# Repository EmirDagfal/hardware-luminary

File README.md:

# hardware-luminary
Diseño PCB en kicad de fotocelula LoRa

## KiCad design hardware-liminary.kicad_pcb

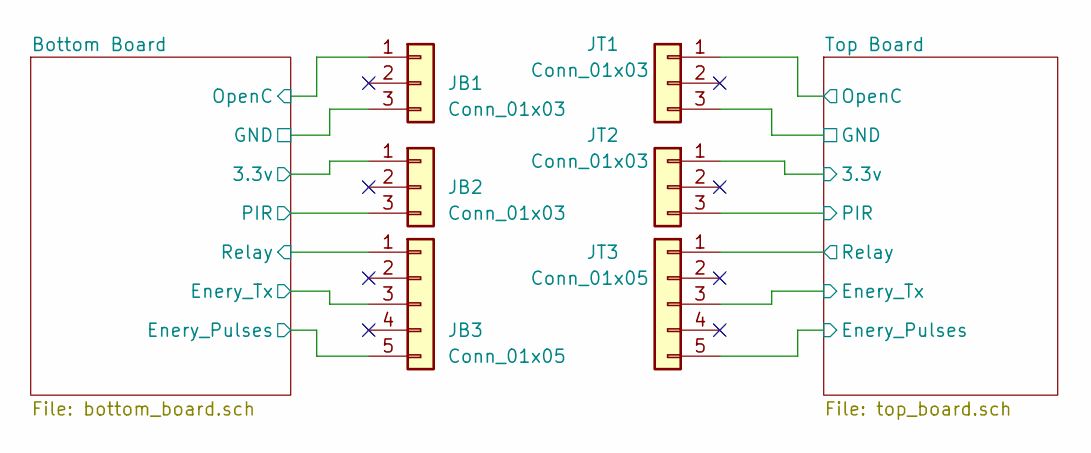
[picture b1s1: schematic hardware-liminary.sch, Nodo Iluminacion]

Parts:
JB1, JB2: Conn_01x03; PinHeader_1x03_P2.54mm_Vertical
JB3: Conn_01x05; PinHeader_1x05_P2.54mm_Vertical
JT1, JT2: Conn_01x03; PinHeader_1x03_P2.54mm_Vertical
JT3: Conn_01x05; PinHeader_1x05_P2.54mm_Vertical

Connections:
/Bottom Board/3.3v: JB2.1; also elsewhere on the board
/Bottom Board/Enery_Pulses: JB3.5; also elsewhere on the board
/Bottom Board/Enery_Tx: JB3.3; also elsewhere on the board
/Bottom Board/OpenC: JB1.1; also elsewhere on the board
/Bottom Board/PIR: JB2.3; also elsewhere on the board
/Bottom Board/Relay: JB3.1; also elsewhere on the board
/Top Board/3.3v: JT2.1; also elsewhere on the board
/Top Board/Enery_Pulses: JT3.5; also elsewhere on the board
/Top Board/Enery_Tx: JT3.3; also elsewhere on the board
/Top Board/OpenC: JT1.1; also elsewhere on the board
/Top Board/PIR: JT2.3; also elsewhere on the board
/Top Board/Relay: JT3.1; also elsewhere on the board
GNDD: JT1.3; also elsewhere on the board
GNDREF: JB1.3; also elsewhere on the board

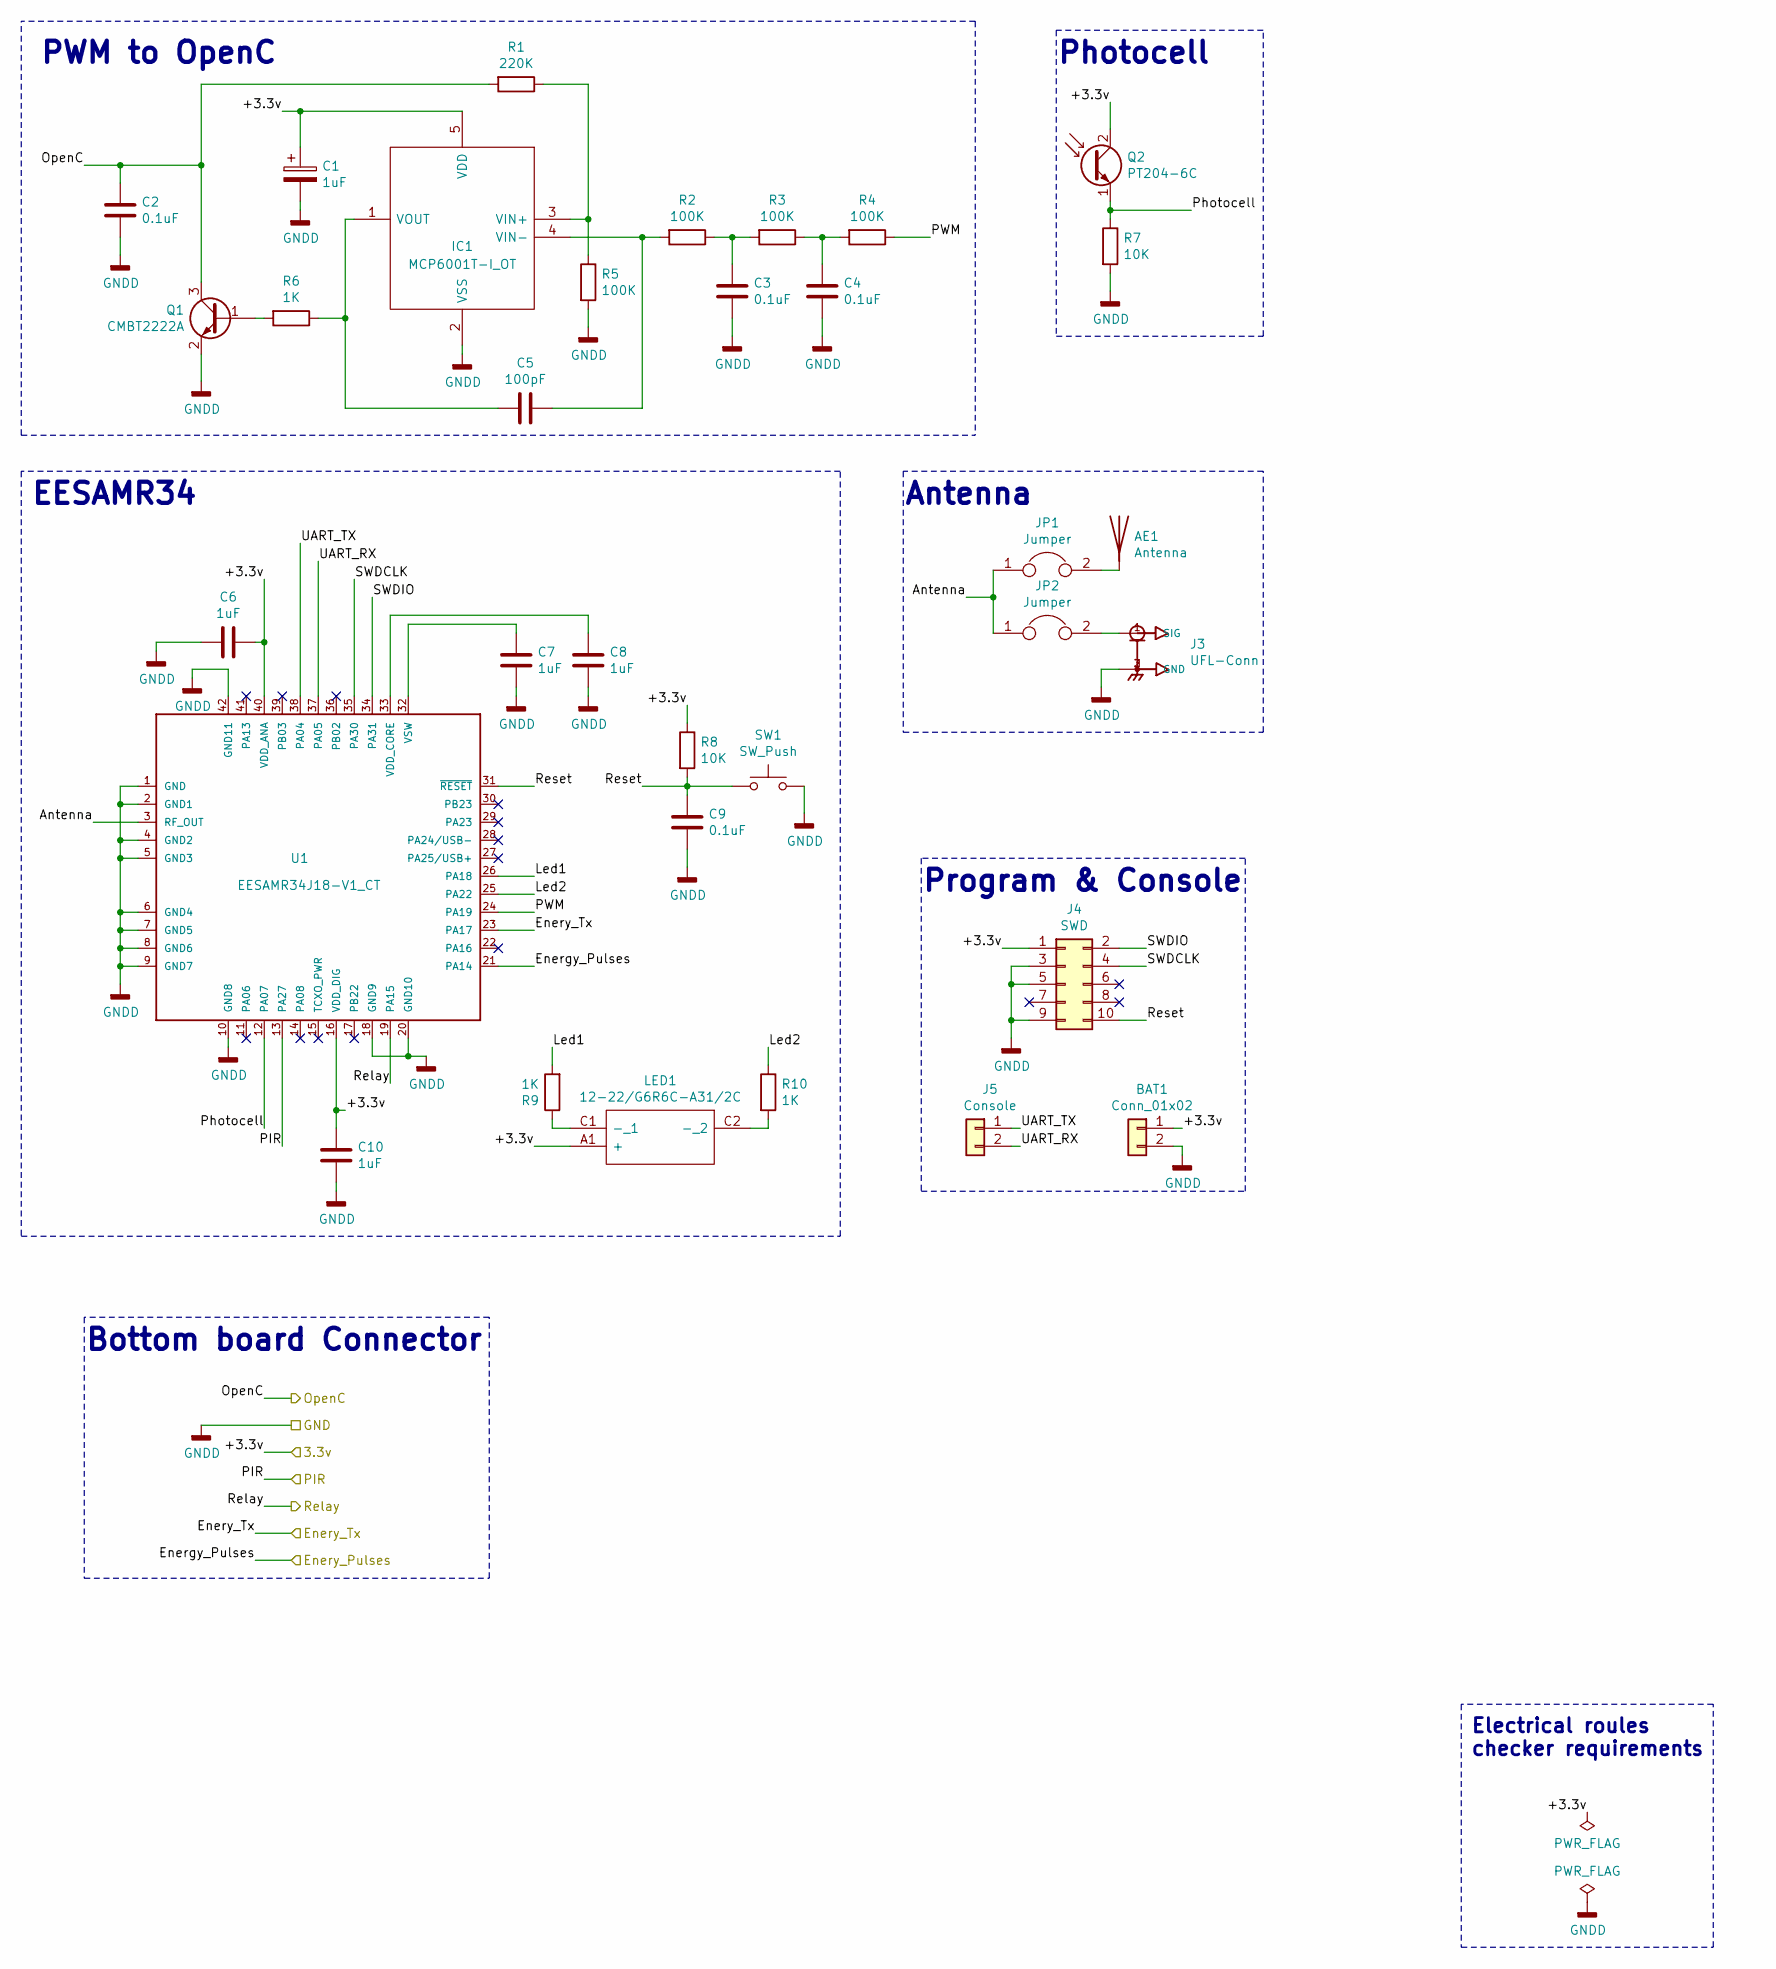
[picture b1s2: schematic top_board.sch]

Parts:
AE1: Antenna; Pin_D1.3mm_L11.0mm_LooseFit
BAT1: Conn_01x02; PinHeader_1x02_P2.54mm_Vertical
C1, C6, C7, C8, C10: 1uF; CP_Elec_4x5.3
C2, C3, C4, C9: 0.1uF; C_0805_2012Metric_Pad1.15x1.40mm_HandSolder
C5: 100pF; C_1206_3216Metric_Pad1.42x1.75mm_HandSolder
IC1: MCP6001T-I_OT; SOT95P270X145-5N; Manufacturer_Part_Number MCP6001T-I/OT; Mouser Part Number 579-MCP6001T-I/OT
J3: UFL-Conn; TE_1909763-1
J4: SWD; PinHeader_2x05_P1.27mm_Vertical
J5: Console; PinHeader_1x02_P2.54mm_Vertical
JP1, JP2: Jumper; R_1206_3216Metric_Pad1.42x1.75mm_HandSolder
LED1: 12-22/G6R6C-A31/2C; 1222SURSYGCS530A2TR8; Manufacturer_Part_Number 12-22SURSYGC/S530-A2/TR8; Mouser Part Number 638-1222SURSYGCA2TR8
Q1: CMBT2222A; SOT-23_Handsoldering
Q2: PT204-6C; LED_D5.0mm_Clear
R1: 220K; R_1206_3216Metric_Pad1.42x1.75mm_HandSolder
R2, R3, R4, R5: 100K; R_1206_3216Metric_Pad1.42x1.75mm_HandSolder
R6, R9, R10: 1K; R_1206_3216Metric_Pad1.42x1.75mm_HandSolder
R7, R8: 10K; R_1206_3216Metric_Pad1.42x1.75mm_HandSolder
SW1: SW_Push; SW_Push_1P1T_NO_6x6mm_H9.5mm
U1: EESAMR34J18-V1_CT; EESAMR34

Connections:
/Top Board/3.3v: BAT1.1, C1.1, C6.2, C10.1, IC1.5 (VDD), J4.1, LED1.A1 (+), Q2.2 (C), R8.1, U1.16 (VDD_DIG), U1.40 (VDD_ANA); also elsewhere on the board
/Top Board/Antenna: JP1.1, JP2.1, U1.3 (RF_OUT)
/Top Board/Enery_Pulses: U1.21 (PA14); also elsewhere on the board
/Top Board/Enery_Tx: U1.23 (PA17); also elsewhere on the board
/Top Board/Led1: R9.2, U1.26 (PA18)
/Top Board/Led2: R10.1, U1.25 (PA22)
/Top Board/OpenC: C2.2, Q1.3 (C), R1.2; also elsewhere on the board
/Top Board/PIR: U1.13 (PA27); also elsewhere on the board
/Top Board/PWM: R4.1, U1.24 (PA19)
/Top Board/Photocell: Q2.1 (E), R7.1, U1.12 (PA07)
/Top Board/Relay: U1.19 (PA15); also elsewhere on the board
/Top Board/Reset: C9.1, J4.10, R8.2, SW1.1, U1.31 (~RESET~)
/Top Board/SWDCLK: J4.4, U1.35 (PA30)
/Top Board/SWDIO: J4.2, U1.34 (PA31)
/Top Board/UART_RX: J5.2, U1.37 (PA05)
/Top Board/UART_TX: J5.1, U1.38 (PA04)
GNDD: BAT1.2, C1.2, C2.1, C3.2, C4.2, C6.1, C7.2, C8.2, C9.2, C10.2, IC1.2 (VSS), J3.2 (GND), J3.3 (GND), J4.3, J4.5, J4.9, Q1.2 (E), R5.2, R7.2, SW1.2, U1.1 (GND), U1.2 (GND1), U1.4 (GND2), U1.5 (GND3), U1.6 (GND4), U1.7 (GND5), U1.8 (GND6), U1.9 (GND7), U1.10 (GND8), U1.18 (GND9), U1.20 (GND10), U1.42 (GND11); also elsewhere on the board
unnamed: AE1.1, JP1.2
unnamed: C3.1, R2.1, R3.2
unnamed: C4.1, R3.1, R4.2
unnamed: C5.1, IC1.4 (VIN-), R2.2
unnamed: C5.2, IC1.1 (VOUT), R6.1
unnamed: C7.1, U1.32 (VSW)
unnamed: C8.1, U1.33 (VDD_CORE)
unnamed: IC1.3 (VIN+), R1.1, R5.1
unnamed: J3.1 (SIG), JP2.2
unnamed: LED1.C1 (-_1), R9.1
unnamed: LED1.C2 (-_2), R10.2
unnamed: Q1.1 (B), R6.2

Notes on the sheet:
Photocell
PWM to OpenC
Program & Console
Antenna
Electrical roules checker requirements
Bottom board Connector
EESAMR34

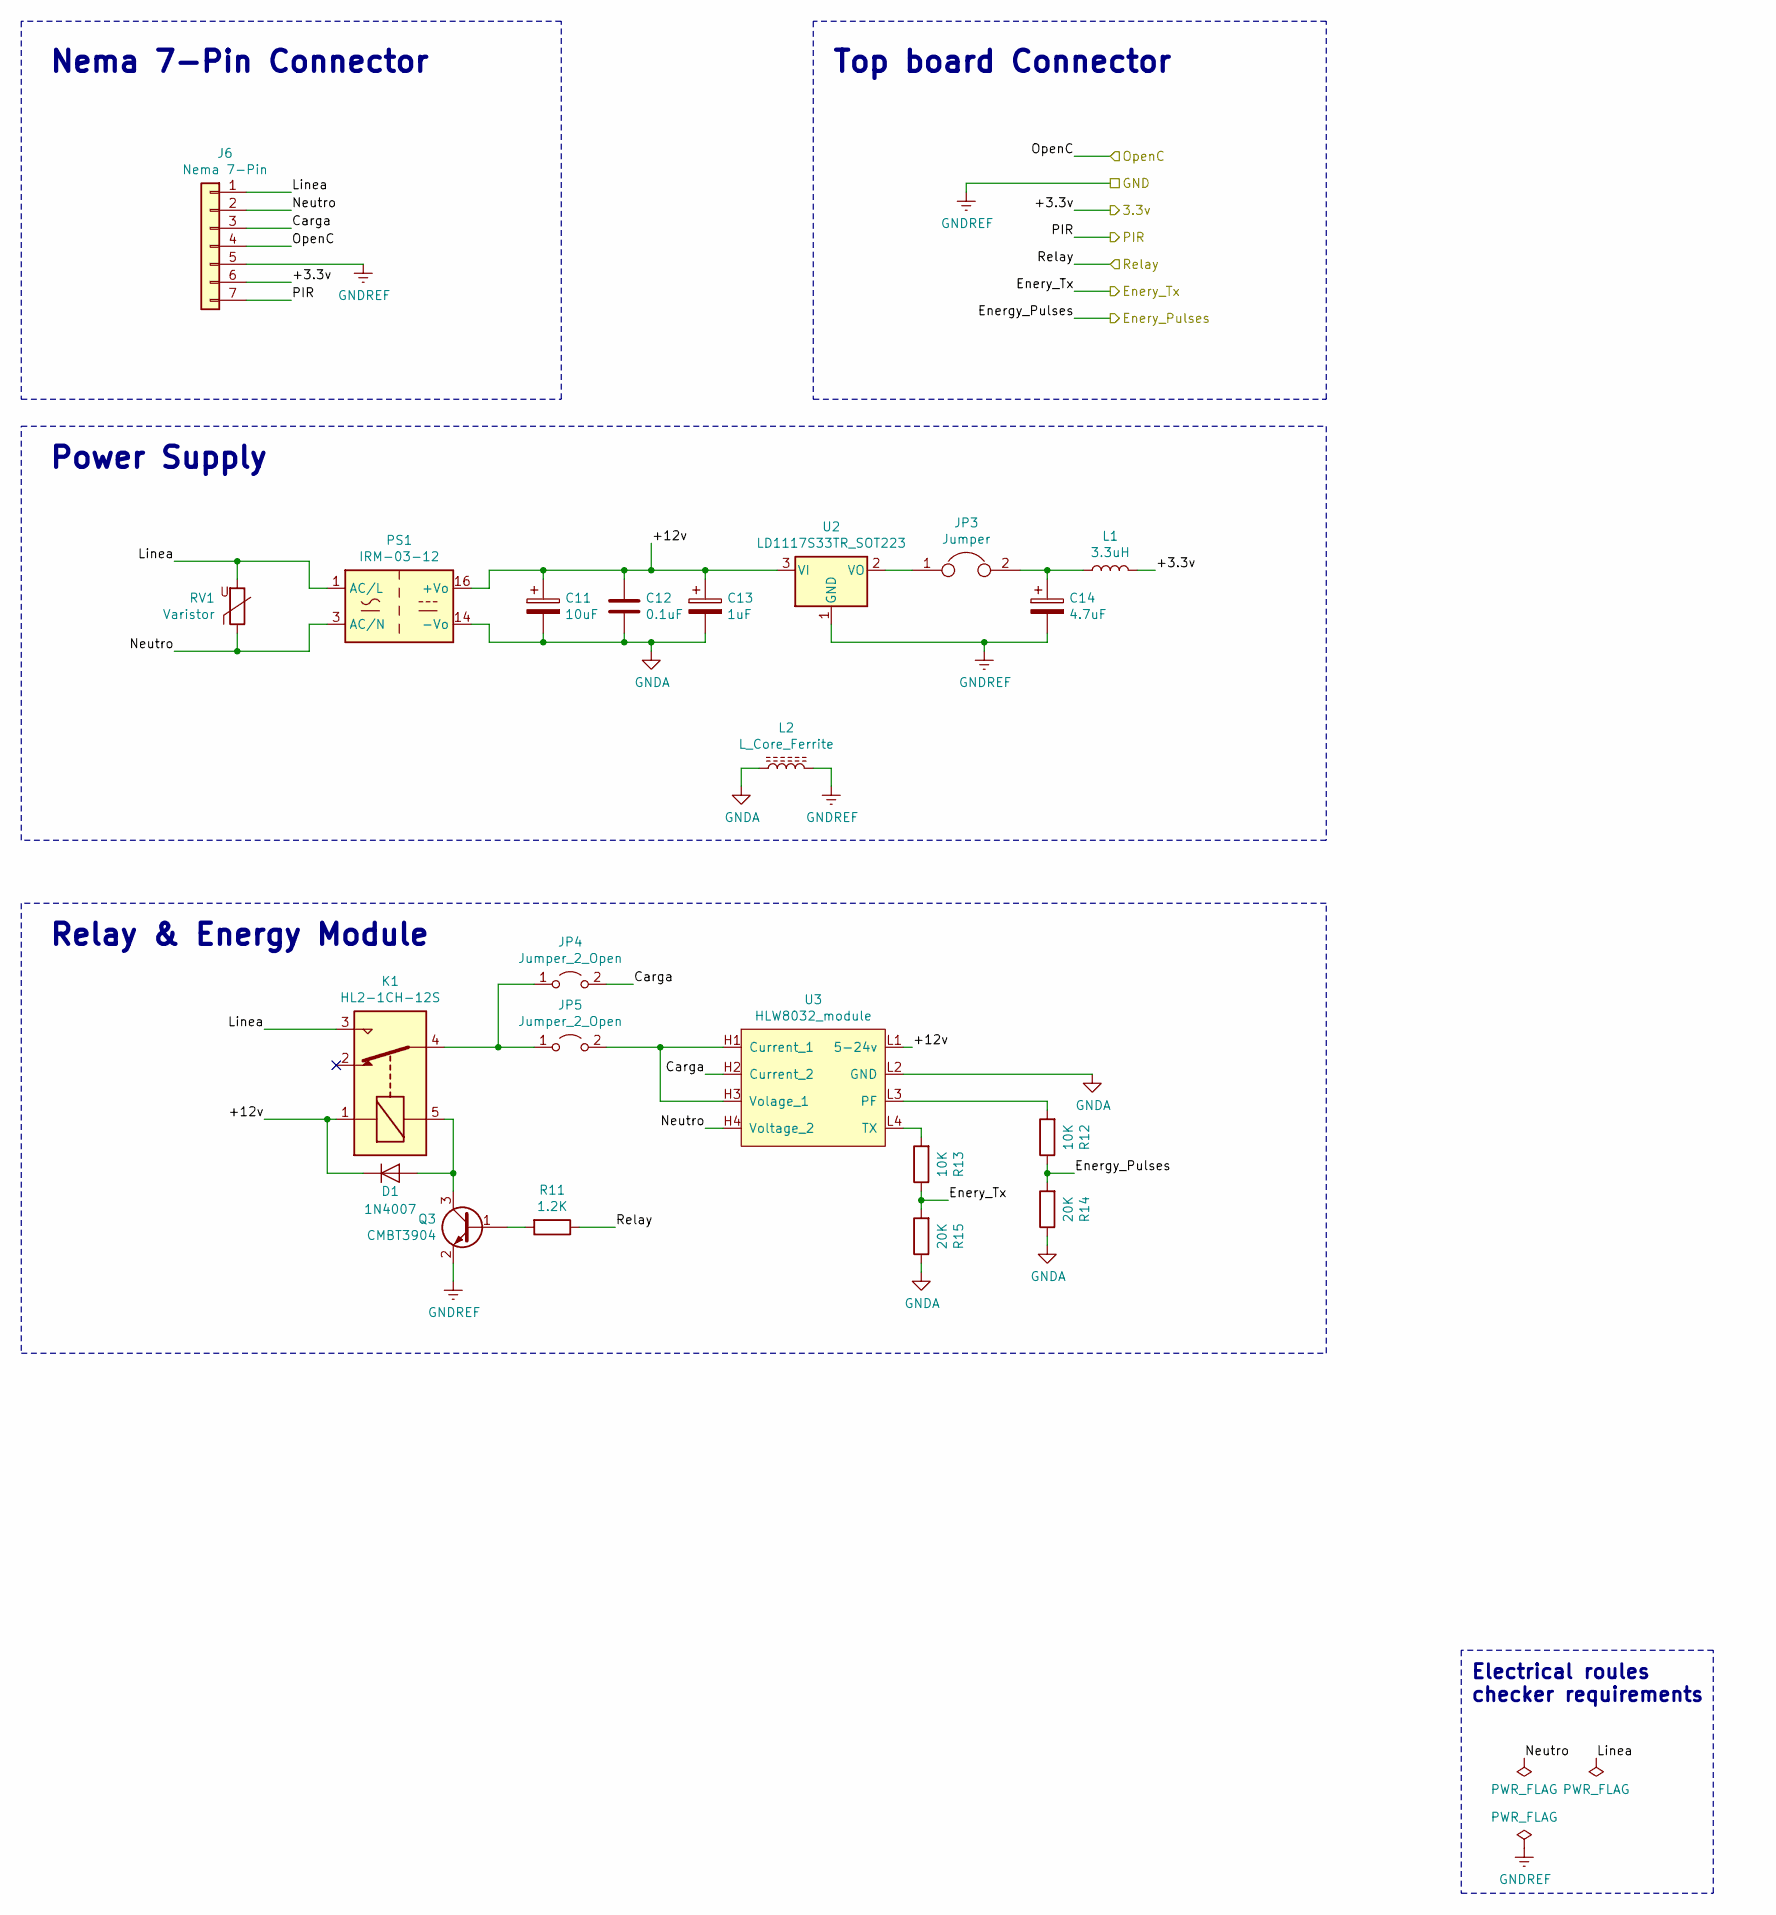
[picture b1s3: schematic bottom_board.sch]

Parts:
C11: 10uF; CP_Radial_D5.0mm_P2.00mm
C12: 0.1uF; C_0805_2012Metric_Pad1.15x1.40mm_HandSolder
C13: 1uF; CP_Elec_4x5.3
C14: 4.7uF; CP_Elec_4x5.4
D1: 1N4007; D_DO-41_SOD81_P10.16mm_Horizontal
J6: Nema 7-Pin; Nema_7-pin
JP3: Jumper; PinHeader_1x02_P2.54mm_Vertical
JP4, JP5: Jumper_2_Open; SolderJumper-2_P1.3mm_Open_Pad1.0x1.5mm
K1: HL2-1CH-12S; Relay_Handouk_HL2-1CH
L1: 3.3uH; L_Taiyo-Yuden_MD-2020
L2: L_Core_Ferrite; L_0805_2012Metric_Pad1.15x1.40mm_HandSolder
PS1: IRM-03-12; Converter_ACDC_MeanWell_IRM-03-xx_THT
Q3: CMBT3904; SOT-23_Handsoldering
R11: 1.2K; R_1206_3216Metric_Pad1.42x1.75mm_HandSolder
R12, R13: 10K; R_1206_3216Metric_Pad1.42x1.75mm_HandSolder
R14, R15: 20K; R_1206_3216Metric_Pad1.42x1.75mm_HandSolder
RV1: Varistor; RV_Disc_D15.5mm_W3.9mm_P7.5mm
U2: LD1117S33TR_SOT223; SOT-23_Handsoldering
U3: HLW8032_module; HLW8032_module_vertical

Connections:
/Bottom Board/3.3v: J6.6, L1.2; also elsewhere on the board
/Bottom Board/+12v: C11.1, C12.1, C13.1, D1.1 (K), K1.1, PS1.16 (+Vo), U2.3 (VI), U3.L1 (5-24v)
/Bottom Board/Carga: J6.3, JP4.2 (B), U3.H2 (Current_2)
/Bottom Board/Enery_Pulses: R12.1, R14.2; also elsewhere on the board
/Bottom Board/Enery_Tx: R13.1, R15.2; also elsewhere on the board
/Bottom Board/Linea: J6.1, K1.3, PS1.1 (AC/L), RV1.2
/Bottom Board/Neutro: J6.2, PS1.3 (AC/N), RV1.1, U3.H4 (Voltage_2)
/Bottom Board/OpenC: J6.4; also elsewhere on the board
/Bottom Board/PIR: J6.7; also elsewhere on the board
/Bottom Board/Relay: R11.1; also elsewhere on the board
GNDA: C11.2, C12.2, C13.2, L2.1, PS1.14 (-Vo), R14.1, R15.1, U3.L2 (GND)
GNDREF: C14.2, J6.5, L2.2, Q3.2 (E), U2.1 (GND); also elsewhere on the board
unnamed: C14.1, JP3.2, L1.1
unnamed: D1.2 (A), K1.5, Q3.3 (C)
unnamed: JP3.1, U2.2 (VO)
unnamed: JP4.1 (A), JP5.1 (A), K1.4
unnamed: JP5.2 (B), U3.H1 (Current_1), U3.H3 (Volage_1)
unnamed: Q3.1 (B), R11.2
unnamed: R12.2, U3.L3 (PF)
unnamed: R13.2, U3.L4 (TX)

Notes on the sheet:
Power Supply
Relay & Energy Module
Electrical roules checker requirements
Nema 7-Pin Connector
Top board Connector

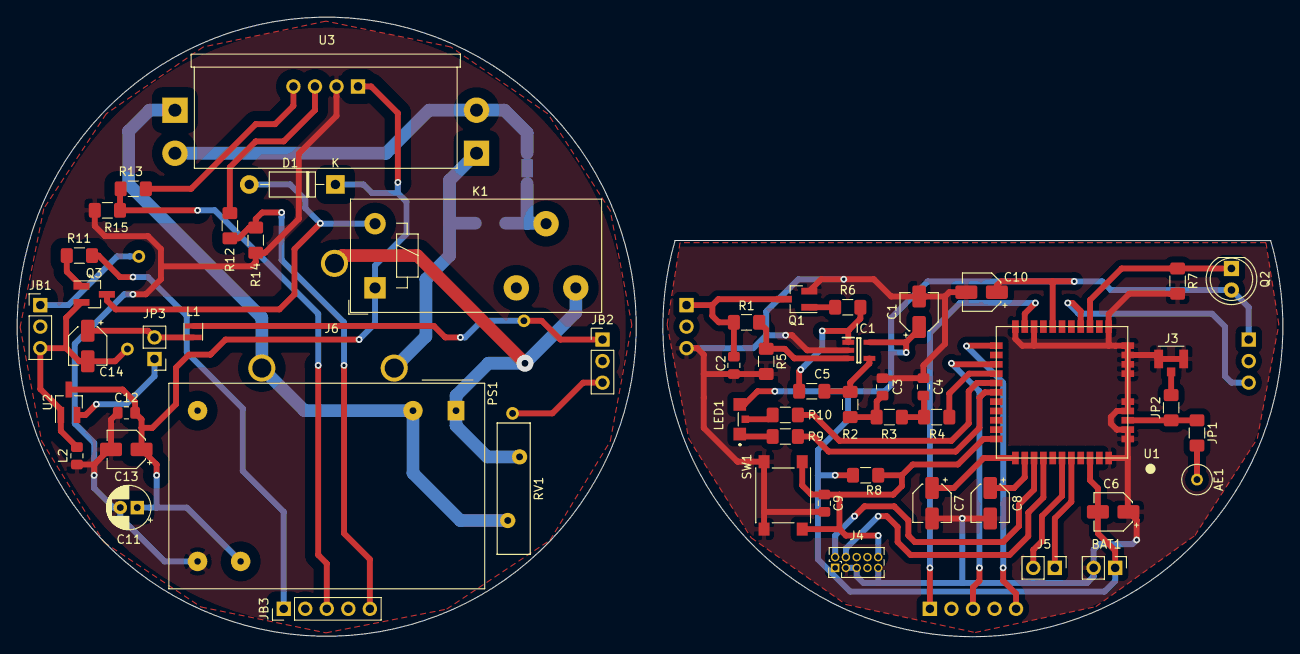
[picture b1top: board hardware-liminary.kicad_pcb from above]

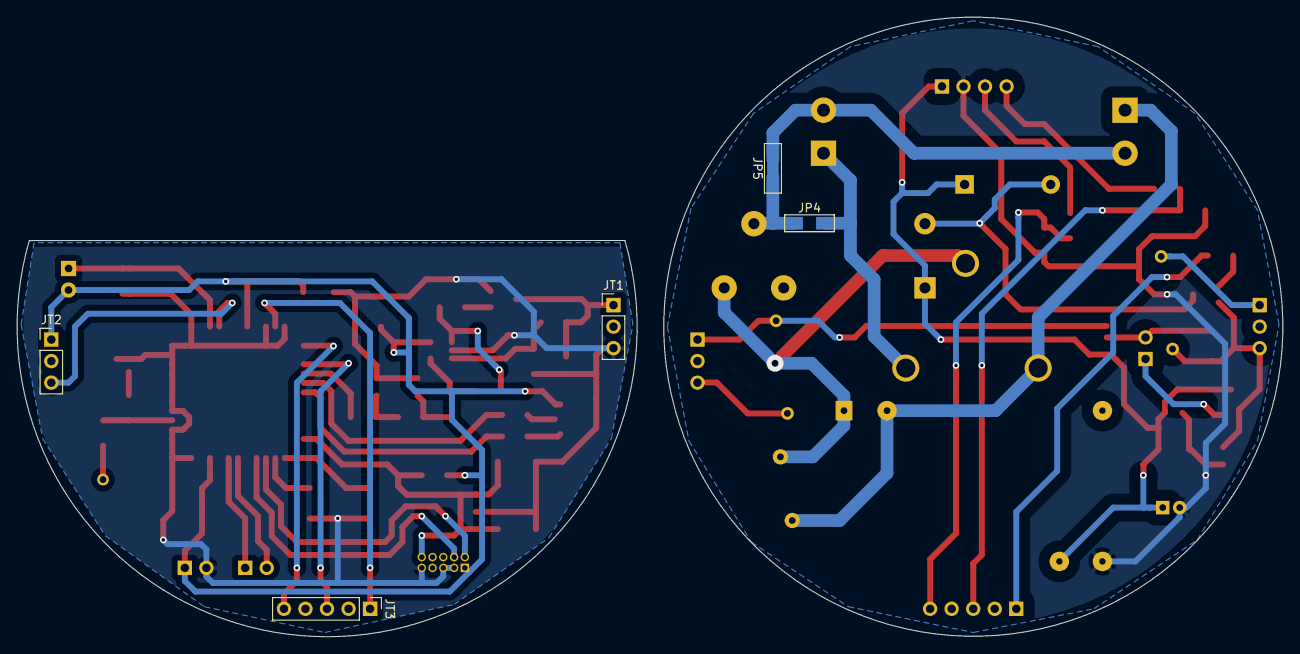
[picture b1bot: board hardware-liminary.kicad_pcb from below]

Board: 2 copper layers, 149.3 x 73.1 mm, 61 parts (5 on the bottom side), 49 nets.

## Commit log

2020-09-30 Primer esquematico completo
    Esta primer version es practicamente una copia del esquematico
    del nodo SmartCell-xDot.
    Falta implementar la medicion de corriente.
2020-09-30 Agregada libreria de IRM-03-12
2020-09-30 Asociadas footprint de componentes standard
2020-09-30 eesam34
2020-10-01 opAmp
2020-10-01 ufl connector
2020-10-01 power supply
2020-10-01 Leds
2020-10-01 power supply 3D
2020-10-01 modelos 3D de ficha ufl y opAmp
2020-10-01 power supply reemplazada por standard
2020-10-01 relay
2020-10-01 Todas las footprint asignadas
2020-10-01 Agregado footprint de base Nema 7-pin
2020-10-02 Esquematico separado en dos placas
2020-10-05 Agregado modulo HLW8032
2020-10-05 Esquematico reordenado
2020-10-06 completado pcb
2020-10-06 Correciones menores
2020-10-06 conector nema rotado y reordenada la placa superior
2020-10-08 Agregado modulo de medicion de energia a pcb
2020-10-09 optimizacion de pistas
2020-10-14 Mejoras en ruteo
